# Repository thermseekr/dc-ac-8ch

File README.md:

# DC-AC-8CH

Triac board with 8x 24 VDC inputs and 8x 220 AC outputs.

## LICENSE

This project is licensed under the [Creative Commons BY-NC 4.0 License](https://creativecommons.org/licenses/by-nc/4.0/).
Commercial use is not permitted without prior written consent. See the [LICENSE.txt](LICENSE.txt) file for details.

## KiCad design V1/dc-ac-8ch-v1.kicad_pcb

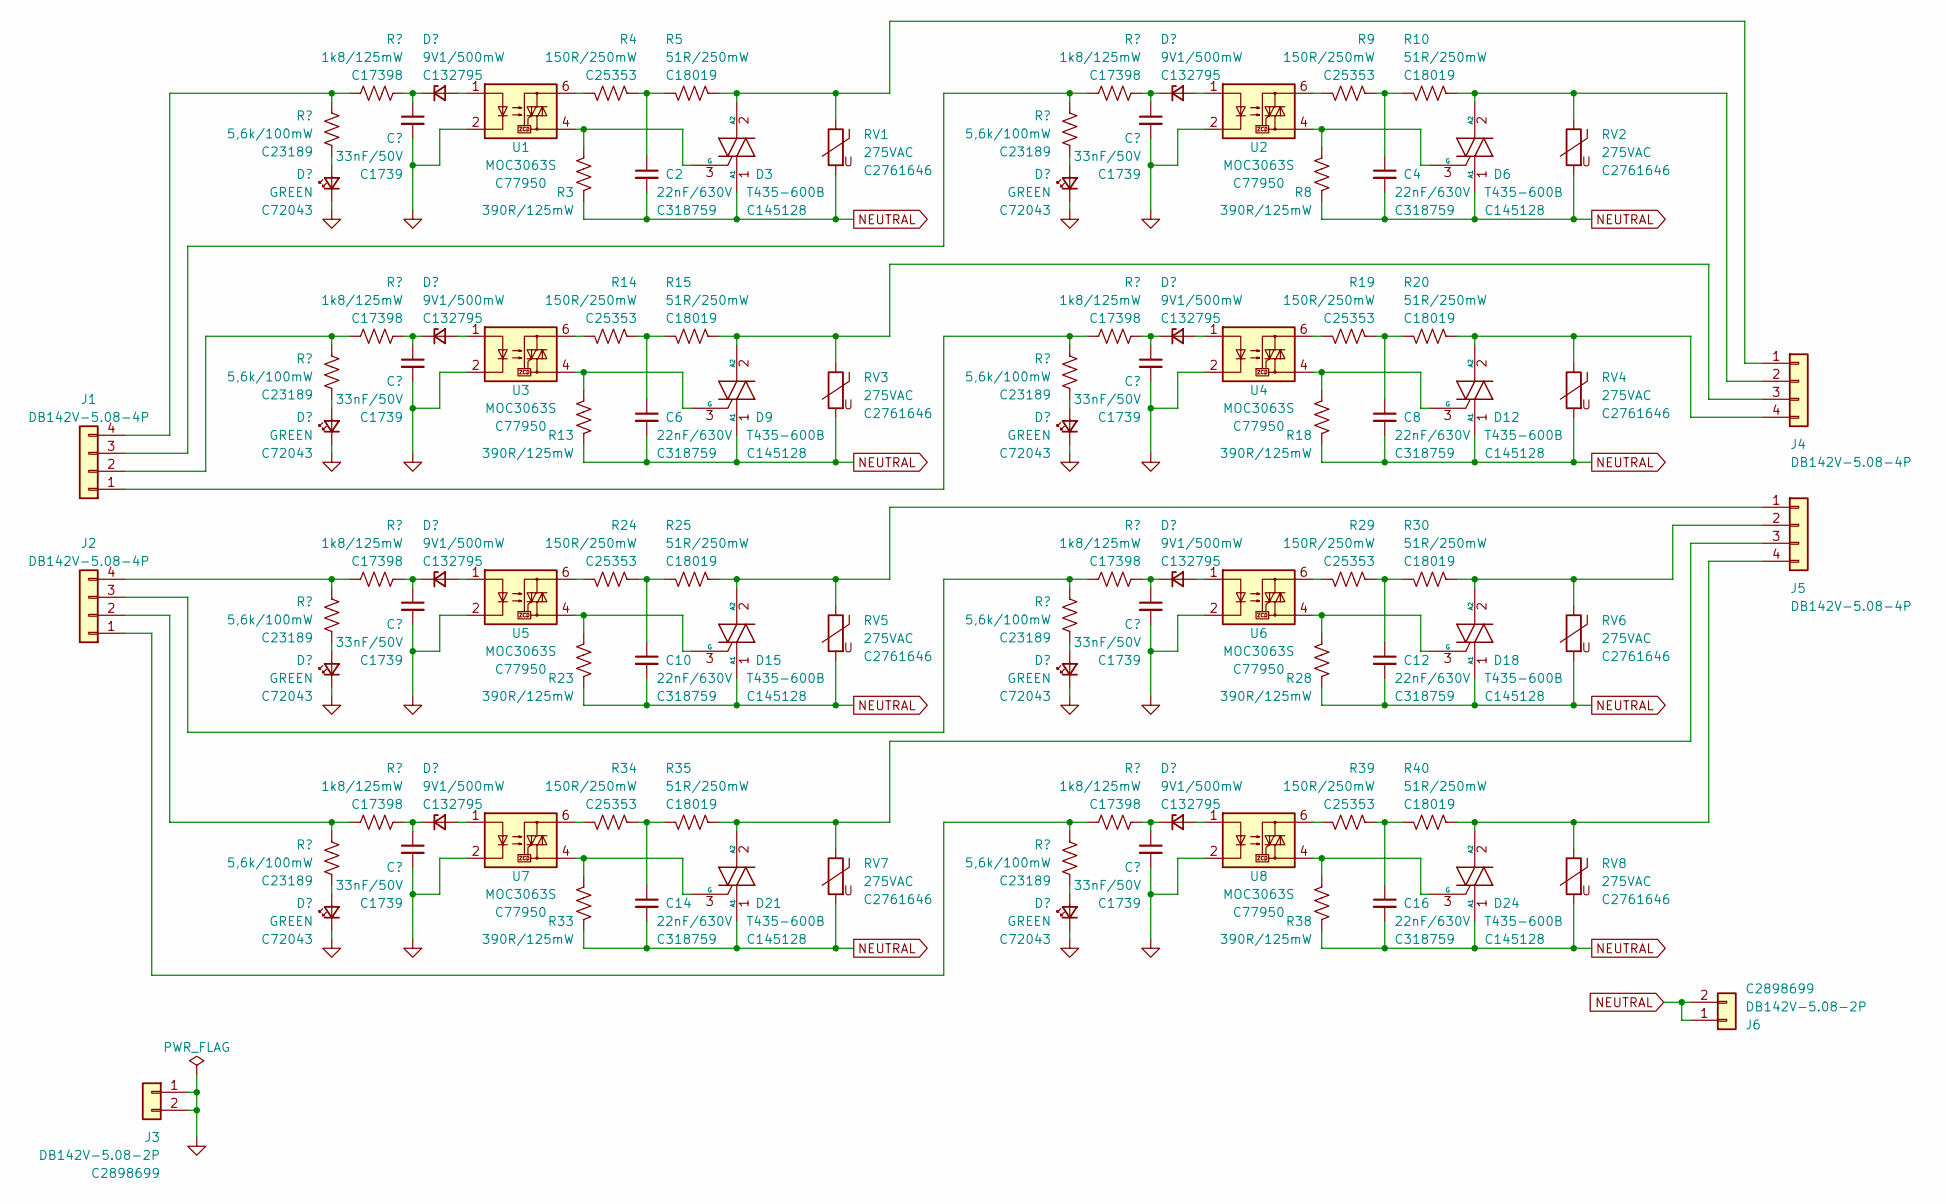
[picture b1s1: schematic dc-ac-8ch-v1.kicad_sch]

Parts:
C1, C3, C5, C7, C9, C11, C13, C15: 33nF/50V; C_0805_2012Metric; LCSC Part # C1739
C2, C4, C6, C8, C10, C12, C14, C16: 22nF/630V; C_1206_3216Metric; Mfr Part # CL31B223KHHNNNE; JLCPCB BOM 1
D1, D4, D7, D10, D13, D16, D19, D22: GREEN; LED_0603_1608Metric; Mfr Part # 19-217/GHC-YR1S2/3T; LCSC Part # C72043
D2, D5, D8, D11, D14, D17, D20, D23: 9V1/500mW; D_SOD-123; Mfr Part # MMSZ9V1T1G; JLCPCB BOM 1
D3, D6, D9, D12, D15, D18, D21, D24: T435-600B; TO-252-2; Mfr Part # T435-600B-TR; JLCPCB BOM 1
J1, J2, J4, J5: DB142V-5.08-4P; TerminalBlock_Dibo_DB142V-5.08-4P_1x04_P5.08mm_Vertical; Mfr Part # DB142V-5.08-4P; JLCPCB BOM 1
J3, J6: DB142V-5.08-2P; TerminalBlock_Dibo_DB142V-5.08-2P_1x02_P5.08mm_Vertical; Mfr Part # DB142V-5.08-2P; JLCPCB BOM 1
R1, R6, R11, R16, R21, R26, R31, R36: 5,6k/100mW; R_0603_1608Metric; Mfr Part # 0603WAF5601T5E; LCSC Part # C23189
R2, R7, R12, R17, R22, R27, R32, R37: 1k8/125mW; R_0805_2012Metric; Mfr Part # 0805W8F1801T5E; LCSC Part # C17398
R3, R8, R13, R18, R23, R28, R33, R38: 390R/125mW; R_0805_2012Metric; Mfr Part # 0805W8F3900T5E; JLCPCB BOM 1
R4, R9, R14, R19, R24, R29, R34, R39: 150R/250mW; R_1206_3216Metric; Mfr Part # 1206W4J0151T5E; JLCPCB BOM 1
R5, R10, R15, R20, R25, R30, R35, R40: 51R/250mW; R_1206_3216Metric; Mfr Part # 1206W4F510JT5E; JLCPCB BOM 1
RV1, RV2, RV3, RV4, RV5, RV6, RV7, RV8: 275VAC; RV_Disc_D9.50mm_W3.6mm_P5.08mm; Mfr Part # RM07D431KC1IE100; JLCPCB BOM 1
U1, U2, U3, U4, U5, U6, U7, U8: MOC3063S; SMDIP-6_W9.53mm_Clearance8mm; Mfr Part # MOC3063S-TA1; JLCPCB BOM 1

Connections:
GND: C1.2, C3.2, C5.2, C7.2, C9.2, C11.2, C13.2, C15.2, D1.1 (K), D4.1 (K), D7.1 (K), D10.1 (K), D13.1 (K), D16.1 (K), D19.1 (K), D22.1 (K), J3.1, J3.2, U1.2, U2.2, U3.2, U4.2, U5.2, U6.2, U7.2, U8.2
NEUTRAL: C2.2, C4.2, C6.2, C8.2, C10.2, C12.2, C14.2, C16.2, D3.1 (A1), D6.1 (A1), D9.1 (A1), D12.1 (A1), D15.1 (A1), D18.1 (A1), D21.1 (A1), D24.1 (A1), J6.1, J6.2, R3.2, R8.2, R13.2, R18.2, R23.2, R28.2, R33.2, R38.2, RV1.2, RV2.2, RV3.2, RV4.2, RV5.2, RV6.2, RV7.2, RV8.2
unnamed: C2.1, R4.1, R5.2
unnamed: C4.1, R9.1, R10.2
unnamed: C6.1, R14.1, R15.2
unnamed: C8.1, R19.1, R20.2
unnamed: C10.1, R24.1, R25.2
unnamed: C12.1, R29.1, R30.2
unnamed: C14.1, R34.1, R35.2
unnamed: C16.1, R39.1, R40.2
unnamed: D1.2 (A), R1.2
unnamed: D2.2 (A), U1.1
unnamed: C1.1, D2.1 (K), R2.1
unnamed: D3.2 (A2), J4.1, R5.1, RV1.1
unnamed: D3.3 (G), R3.1, U1.4
unnamed: D4.2 (A), R6.2
unnamed: D5.2 (A), U2.1
unnamed: C3.1, D5.1 (K), R7.1
unnamed: D6.2 (A2), J4.2, R10.1, RV2.1
unnamed: D6.3 (G), R8.1, U2.4
unnamed: D7.2 (A), R11.2
unnamed: D8.2 (A), U3.1
unnamed: C5.1, D8.1 (K), R12.1
unnamed: D9.2 (A2), J4.3, R15.1, RV3.1
unnamed: D9.3 (G), R13.1, U3.4
unnamed: D10.2 (A), R16.2
unnamed: D11.2 (A), U4.1
unnamed: C7.1, D11.1 (K), R17.1
unnamed: D12.2 (A2), J4.4, R20.1, RV4.1
unnamed: D12.3 (G), R18.1, U4.4
unnamed: D13.2 (A), R21.2
unnamed: D14.2 (A), U5.1
unnamed: C9.1, D14.1 (K), R22.1
unnamed: D15.2 (A2), J5.1, R25.1, RV5.1
unnamed: D15.3 (G), R23.1, U5.4
unnamed: D16.2 (A), R26.2
unnamed: D17.2 (A), U6.1
unnamed: C11.1, D17.1 (K), R27.1
unnamed: D18.2 (A2), J5.2, R30.1, RV6.1
unnamed: D18.3 (G), R28.1, U6.4
unnamed: D19.2 (A), R31.2
unnamed: D20.2 (A), U7.1
unnamed: C13.1, D20.1 (K), R32.1
unnamed: D21.2 (A2), J5.3, R35.1, RV7.1
unnamed: D21.3 (G), R33.1, U7.4
unnamed: D22.2 (A), R36.2
unnamed: D23.2 (A), U8.1
unnamed: C15.1, D23.1 (K), R37.1
unnamed: D24.2 (A2), J5.4, R40.1, RV8.1
unnamed: D24.3 (G), R38.1, U8.4
unnamed: J1.1, R16.1, R17.2
unnamed: J1.2, R11.1, R12.2
unnamed: J1.3, R6.1, R7.2
unnamed: J1.4, R1.1, R2.2
unnamed: J2.1, R36.1, R37.2
unnamed: J2.2, R31.1, R32.2
unnamed: J2.3, R26.1, R27.2
unnamed: J2.4, R21.1, R22.2
unnamed: R4.2, U1.6
unnamed: R9.2, U2.6
unnamed: R14.2, U3.6
unnamed: R19.2, U4.6
unnamed: R24.2, U5.6
unnamed: R29.2, U6.6
unnamed: R34.2, U7.6
unnamed: R39.2, U8.6

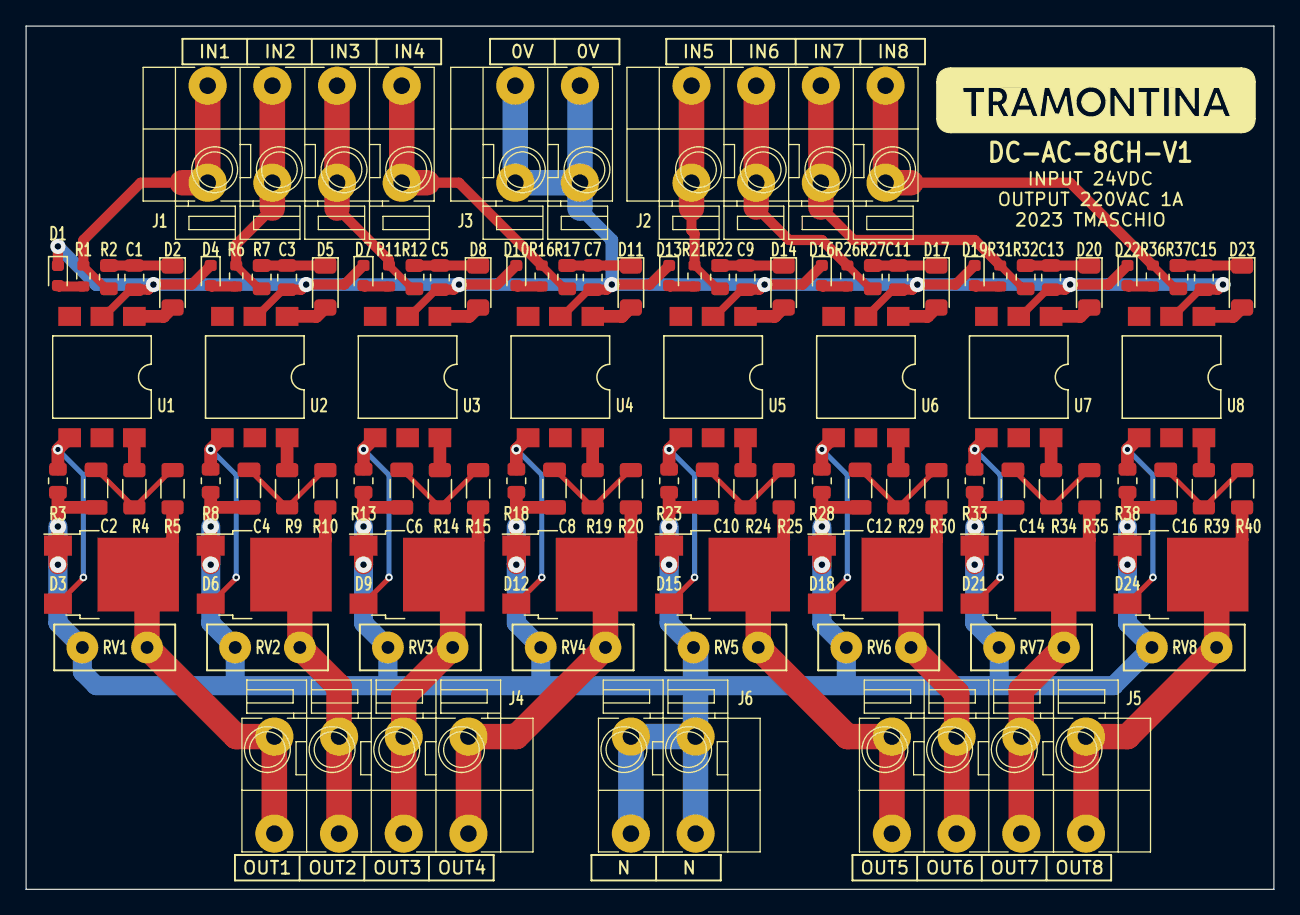
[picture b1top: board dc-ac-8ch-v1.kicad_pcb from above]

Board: 2 copper layers, 98.0 x 67.8 mm, 102 parts (0 on the bottom side), 66 nets.

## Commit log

2023-08-31 New design
2023-08-31 Circuit under dev
2023-08-31 Under development
2023-09-01 Development
2023-09-01 Zener diode replaced
2023-09-01 Replace resistor for basic part
2023-09-04 Layout redone, footprints updated
2023-09-04 New board image
2023-09-05 Updated image
2023-09-06 Place missing track under zone
2023-09-08 Relocate track
2023-09-08 Repo cleanup
2023-09-08 Design completed.
2023-09-15 Final tweaks for production
2025-06-29 Added license
